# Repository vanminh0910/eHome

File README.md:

# eHome
This is reserved repository for my smart home project

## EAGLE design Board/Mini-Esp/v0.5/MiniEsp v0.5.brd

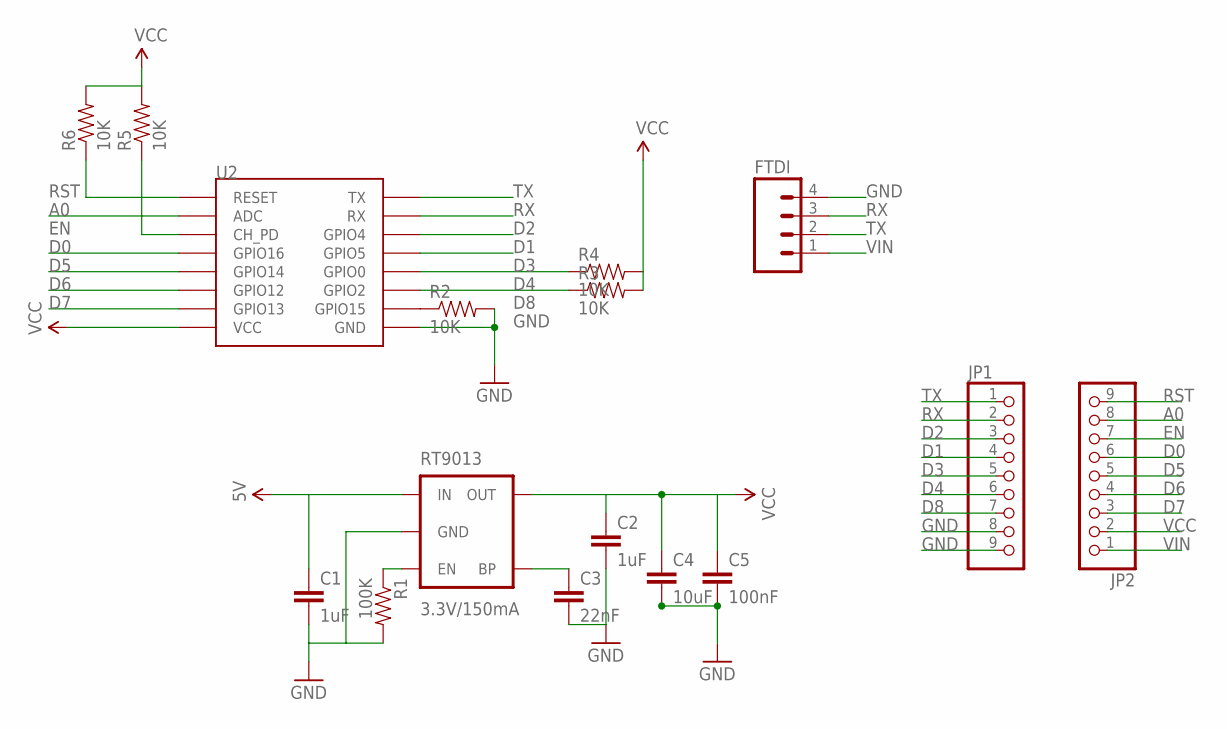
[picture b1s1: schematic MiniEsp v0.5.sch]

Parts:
C1, C2: 1uF; 0805
C3: 22nF; 0805
C4: 10uF; 0805
C5: 100nF; 0805
FTDI: M04PTH; 1X04
JP1, JP2: PINHD-1X9; 1X09-BIG
R1: 100K; 0805
R2, R3, R4, R5, R6: 10K; 0805
RT9013: 3.3V/150mA; SOT23-5
U2: ESP12

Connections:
A0: JP2.8, U2.ADC
BP: C3.1, RT9013.4 (BP)
D0: JP2.6, U2.GPIO16
D1: JP1.4, U2.GPIO5
D2: JP1.3, U2.GPIO4
D3: JP1.5, R4.1, U2.GPIO0
D4: JP1.6, R3.1, U2.GPIO2
D5: JP2.5, U2.GPIO14
D6: JP2.4, U2.GPIO12
D7: JP2.3, U2.GPIO13
D8: JP1.7, R2.1, U2.GPIO15
EN: JP2.7, R5.1, U2.CH_PD
GND: C1.2, C2.2, C3.2, C4.2, C5.2, FTDI.4, JP1.8, JP1.9, R1.2, R2.2, RT9013.2 (GND), U2.GND
LDO_EN: R1.1, RT9013.3 (EN)
RST: JP2.9, R6.1, U2.RESET
RX: FTDI.3, JP1.2, U2.RX
TX: FTDI.2, JP1.1, U2.TX
VCC: C2.1, C4.1, C5.1, JP2.2, R3.2, R4.2, R5.2, R6.2, RT9013.5 (OUT), U2.VCC
VIN: C1.1, FTDI.1, JP2.1, RT9013.1 (IN)

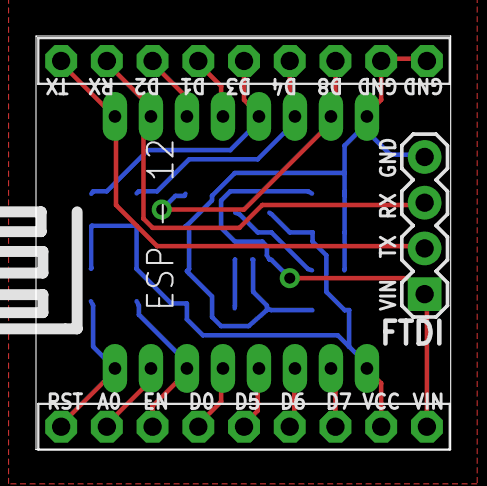
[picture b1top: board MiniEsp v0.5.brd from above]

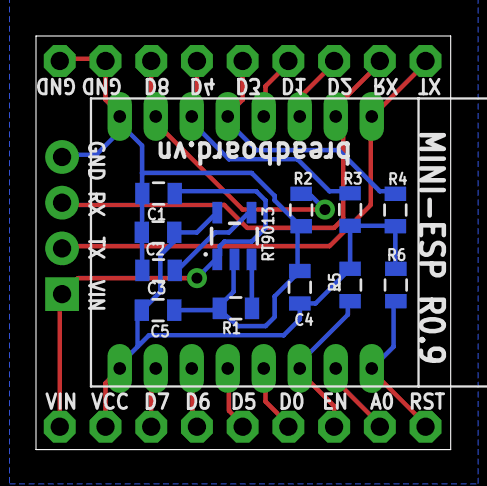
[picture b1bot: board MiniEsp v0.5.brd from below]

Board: 2 copper layers, 23.0 x 23.0 mm, 16 parts (12 on the bottom side), 19 nets.

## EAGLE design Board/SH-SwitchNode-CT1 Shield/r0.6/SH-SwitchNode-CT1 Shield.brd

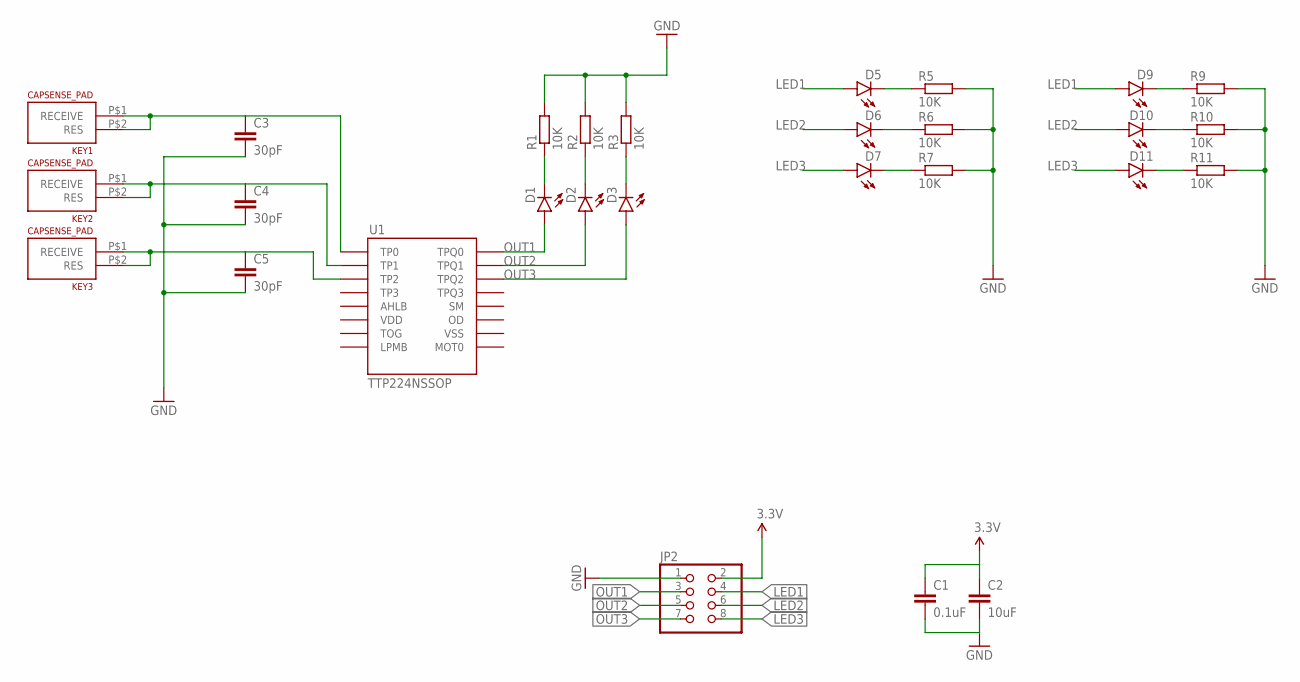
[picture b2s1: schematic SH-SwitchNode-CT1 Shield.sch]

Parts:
C1: 0.1uF; 0805
C2: 10uF; 0805
C3, C4, C5: 30pF; 0805
D1, D2, D3, D5, D6, D7, D9, D10, D11: LED1206-BOTTOM; LED-1206-BOTTOM
JP2: PINHD-2X4; 2X04
KEY1, KEY2, KEY3: CAPSENSE_PAD
R1, R2, R3, R5, R6, R7, R9, R10, R11: 10K; R0805
U1: TTP224NSSOP; SSOP16

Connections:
3.3V: C1.1, C2.1, JP2.2
GND: C1.2, C2.2, C3.2, C4.2, C5.2, JP2.1, R1.2, R2.2, R3.2, R5.2, R6.2, R7.2, R9.2, R10.2, R11.2
KEY1: C3.1, KEY1.P$1 (RECEIVE), KEY1.P$2 (RES), U1.1 (TP0)
KEY2: C4.1, KEY2.P$1 (RECEIVE), KEY2.P$2 (RES), U1.2 (TP1)
KEY3: C5.1, KEY3.P$1 (RECEIVE), KEY3.P$2 (RES), U1.3 (TP2)
LED1: D5.A, D9.A, JP2.4
LED2: D6.A, D10.A, JP2.6
LED3: D7.A, D11.A, JP2.8
unnamed: D5.C, R5.1
unnamed: D6.C, R6.1
unnamed: D1.C, R1.1
unnamed: D7.C, R7.1
unnamed: D9.C, R9.1
unnamed: D2.C, R2.1
unnamed: D3.C, R3.1
unnamed: D10.C, R10.1
unnamed: D11.C, R11.1
OUT1: D1.A, JP2.3, U1.16 (TPQ0)
OUT2: D2.A, JP2.5, U1.15 (TPQ1)
OUT3: D3.A, JP2.7, U1.14 (TPQ2)
VDD: U1.6 (VDD)
VSS: U1.10 (VSS)

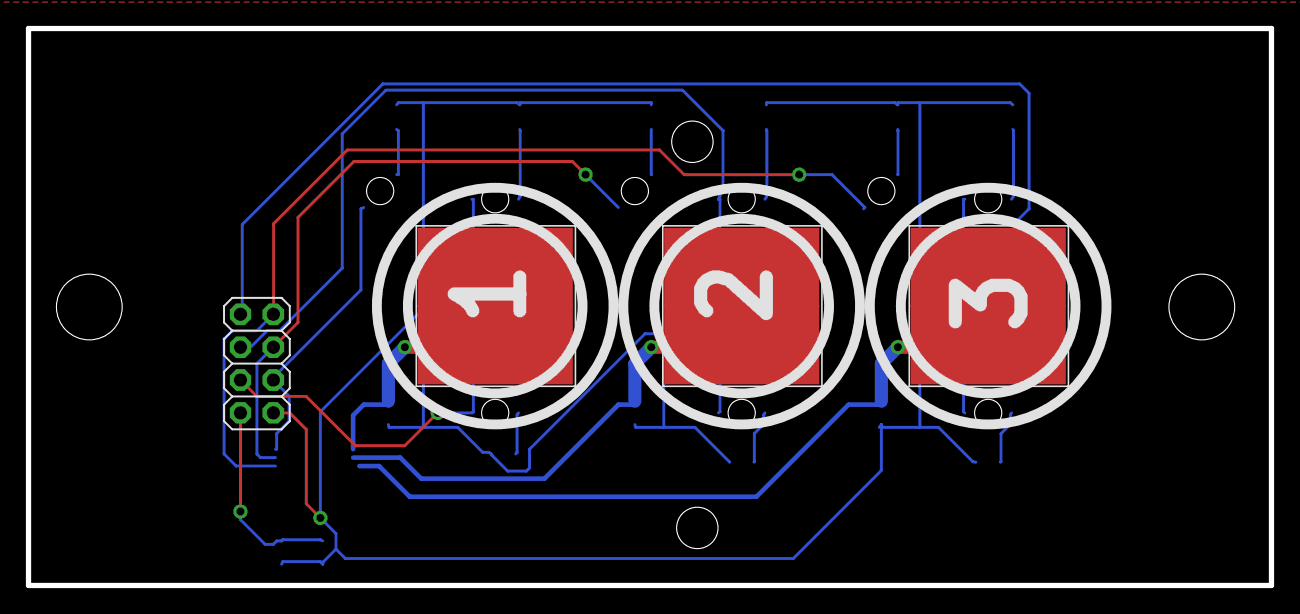
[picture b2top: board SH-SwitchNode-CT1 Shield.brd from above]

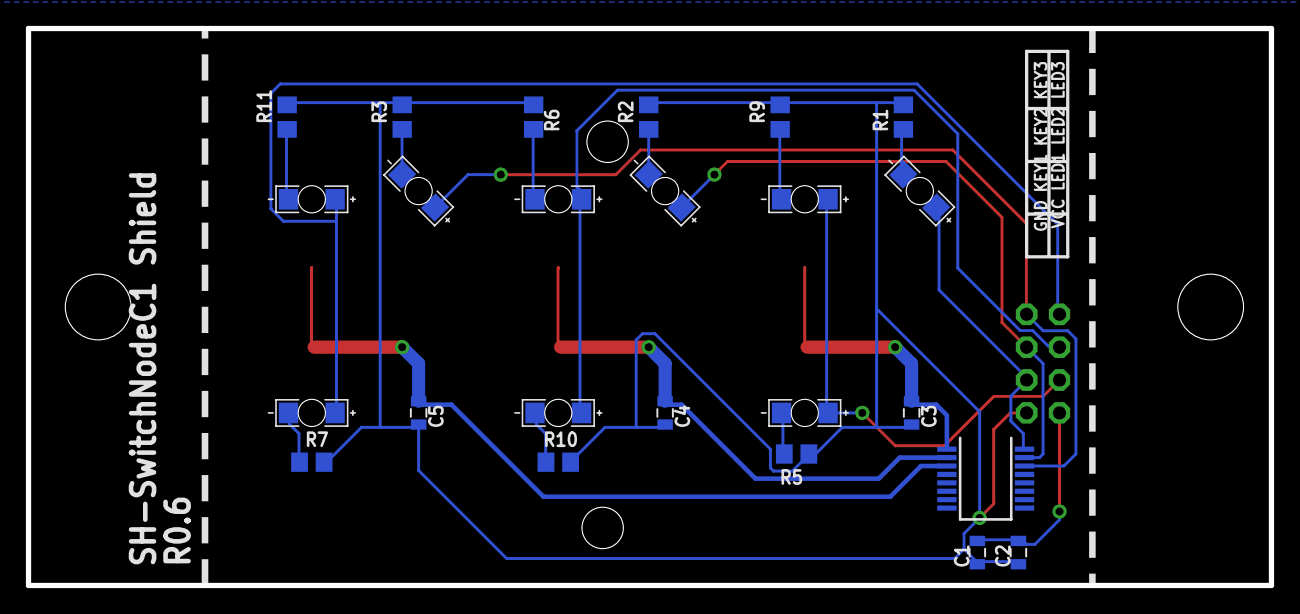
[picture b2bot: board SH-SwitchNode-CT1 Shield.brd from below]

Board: 2 copper layers, 96.1 x 43.0 mm, 28 parts (24 on the bottom side), 20 nets.

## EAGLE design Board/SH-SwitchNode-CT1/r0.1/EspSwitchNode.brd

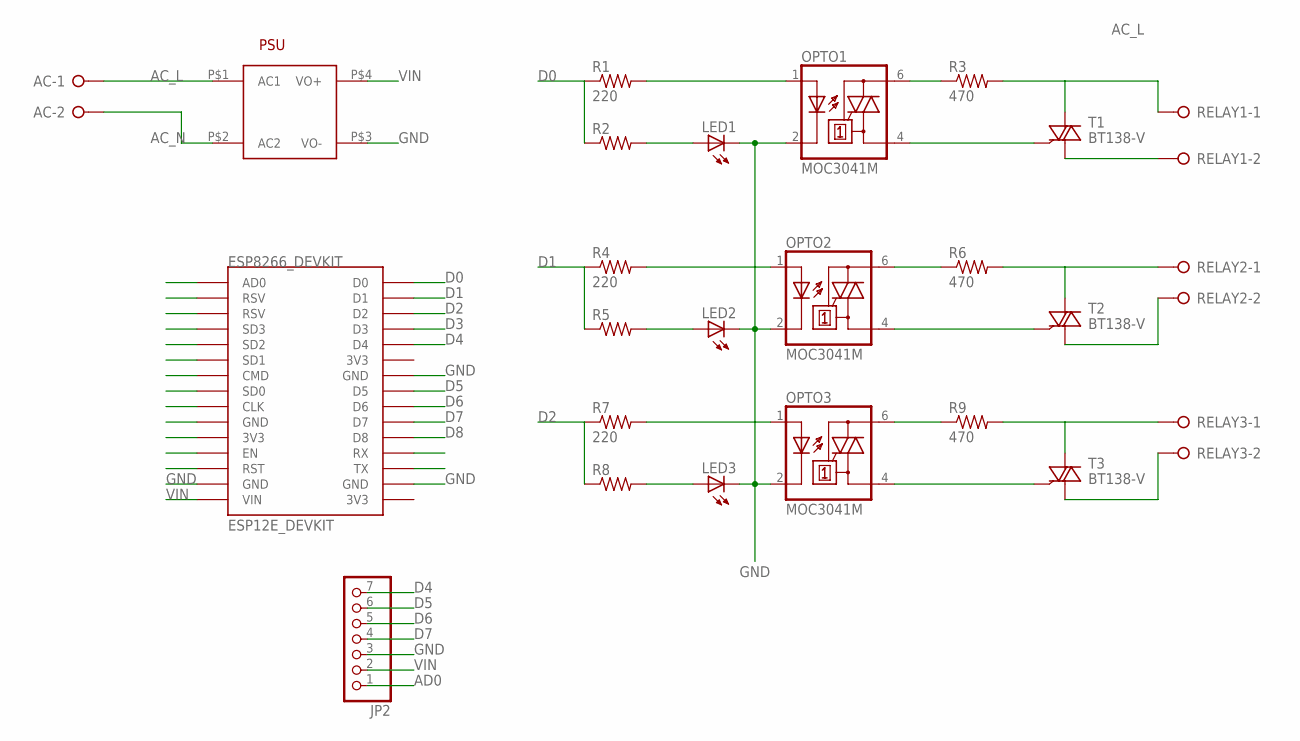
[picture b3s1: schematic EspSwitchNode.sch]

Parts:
AC: W237-02P; W237-132
ESP8266_DEVKIT: ESP12E_DEVKIT
JP2: PINHD-1X7; 1X07
LED1, LED2, LED3: LEDCHIPLED_0805; CHIPLED_0805
OPTO1, OPTO2, OPTO3: MOC3041M; DIL06
PSU: HLK-PM01
R1, R4, R7: 220; M0805
R2, R5, R8: R-US_M0805; M0805
R3, R6, R9: 470; M0805
RELAY1, RELAY2, RELAY3: W237-02P; W237-132
T1, T2, T3: BT138-V; TO220BV

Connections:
3V3: ESP8266_DEVKIT.3V3@0 (3V3)
AC_L: AC.1, PSU.P$1 (AC1), R3.2, R6.2, R9.2, RELAY1.1, RELAY2.1, RELAY3.1, T1.T2 (A2), T2.T2 (A2), T3.T2 (A2)
AC_N: AC.2, PSU.P$2 (AC2)
AD0: ESP8266_DEVKIT.AD0, JP2.1
CLK: ESP8266_DEVKIT.CLK
CMD: ESP8266_DEVKIT.CMD
D0: ESP8266_DEVKIT.D0, R1.1, R2.1
D1: ESP8266_DEVKIT.D1, R4.1, R5.1
D2: ESP8266_DEVKIT.D2, R7.1, R8.1
D3: ESP8266_DEVKIT.D3
D4: ESP8266_DEVKIT.D4, JP2.7
D5: ESP8266_DEVKIT.D5, JP2.6
D6: ESP8266_DEVKIT.D6, JP2.5
D7: ESP8266_DEVKIT.D7, JP2.4
D8: ESP8266_DEVKIT.D8
EN: ESP8266_DEVKIT.EN
GND: ESP8266_DEVKIT.GND@0 (GND), ESP8266_DEVKIT.GND@1 (GND), ESP8266_DEVKIT.GND@2 (GND), ESP8266_DEVKIT.GND@3 (GND), JP2.3, LED1.C, LED2.C, LED3.C, OPTO1.2 (C), OPTO2.2 (C), OPTO3.2 (C), PSU.P$3 (VO-)
unnamed: OPTO1.1 (A), R1.2
unnamed: OPTO1.6 (A2), R3.1
unnamed: OPTO2.1 (A), R4.2
unnamed: LED2.A, R5.2
unnamed: OPTO2.6 (A2), R6.1
unnamed: OPTO1.4 (A1), T1.G
unnamed: OPTO2.4 (A1), T2.G
unnamed: OPTO3.1 (A), R7.2
unnamed: LED3.A, R8.2
unnamed: RELAY2.2, T2.T1 (A1)
unnamed: OPTO3.6 (A2), R9.1
unnamed: OPTO3.4 (A1), T3.G
unnamed: RELAY3.2, T3.T1 (A1)
unnamed: LED1.A, R2.2
unnamed: RELAY1.2, T1.T1 (A1)
RST: ESP8266_DEVKIT.RST
RX: ESP8266_DEVKIT.RX
SD0: ESP8266_DEVKIT.SD0
SD1: ESP8266_DEVKIT.SD1
SD2: ESP8266_DEVKIT.SD2
SD3: ESP8266_DEVKIT.SD3
TX: ESP8266_DEVKIT.TX
VIN: ESP8266_DEVKIT.VIN, JP2.2, PSU.P$4 (VO+)

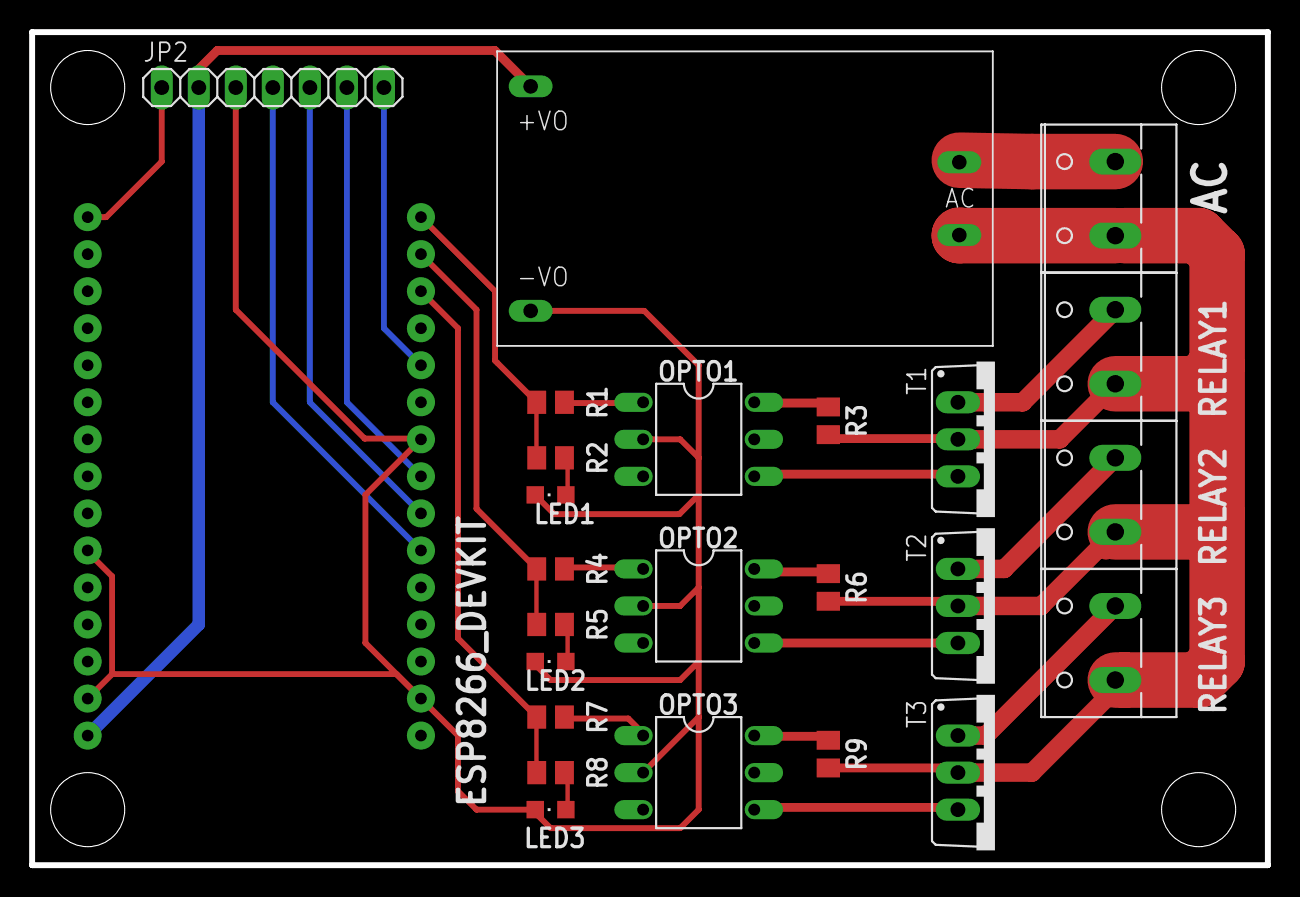
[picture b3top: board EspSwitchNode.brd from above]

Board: 2 copper layers, 84.8 x 57.1 mm, 25 parts (0 on the bottom side), 27 nets.

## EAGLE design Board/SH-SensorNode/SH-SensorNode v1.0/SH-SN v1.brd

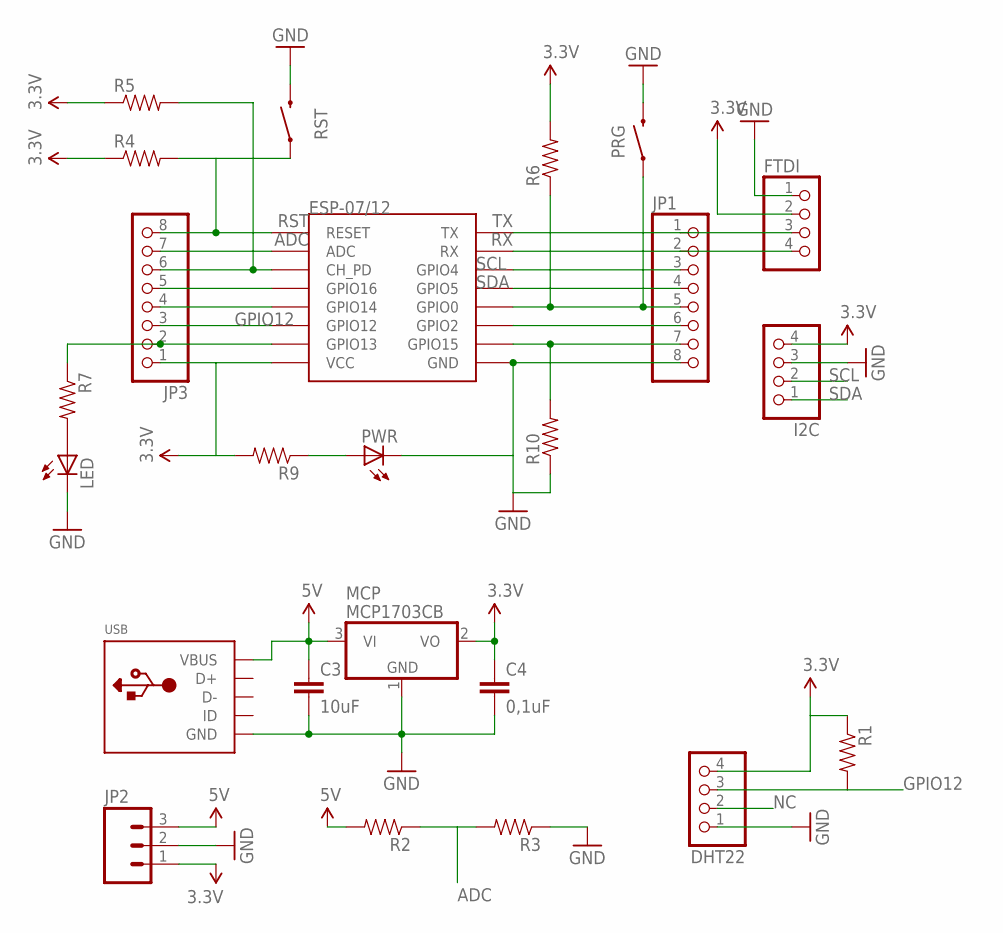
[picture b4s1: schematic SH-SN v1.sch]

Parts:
C3: 10uF; 0805
C4: 0,1uF; 0805
DHT22: PINHD-1X4; 1X04
ESP-07/12: ESP12SMD; ESP12-SMD
FTDI: PINHD-1X4; 1X04
I2C: PINHD-1X4; 1X04
JP1, JP3: PINHD-1X8; 1X08
JP2: M03SCREW; SCREWTERMINAL-3.5MM-3
LED: LEDCHIPLED_0805; CHIPLED_0805
MCP: MCP1703CB; SOT23
PRG: SWITCH-MOMENTARY-2SMD-REDUNDANT; TACTILE-SWITCH-SMD
PWR: LEDCHIPLED_0805; CHIPLED_0805
R1, R2, R3, R4, R5, R6, R7, R9, R10: RESISTOR0805-RES; 0805
RST: SWITCH-MOMENTARY-2SMD-REDUNDANT; TACTILE-SWITCH-SMD
USB: USBMINIB; USB-MINIB

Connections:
3.3V: C4.1, ESP-07/12.VCC, FTDI.2, I2C.4, JP2.1, JP3.1, MCP.2 (VO), R4.1, R5.1, R6.2, R9.2
5V: C3.1, JP2.3, MCP.3 (VI), R2.2, USB.VBUS
ADC: ESP-07/12.ADC, JP3.7, R2.1, R3.2
GND: C3.2, C4.2, DHT22.1, ESP-07/12.GND, FTDI.1, I2C.3, JP1.8, JP2.2, LED.C, MCP.1 (GND), PRG.3 (2), PRG.4 (2), PWR.C, R3.1, R10.1, RST.3 (2), RST.4 (2), USB.GND
GPIO0: ESP-07/12.GPIO13, JP3.2, R7.1
GPIO12: DHT22.3, DHT22.4, ESP-07/12.GPIO12, JP3.3, R1.1, R1.2
unnamed: ESP-07/12.GPIO14, JP3.4
unnamed: ESP-07/12.GPIO2, JP1.6
unnamed: ESP-07/12.GPIO0, JP1.5, PRG.1, PRG.2 (1), R6.1
unnamed: ESP-07/12.CH_PD, JP3.6, R5.2
unnamed: ESP-07/12.GPIO16, JP3.5
unnamed: ESP-07/12.GPIO15, JP1.7, R10.2
unnamed: LED.A, R7.2
unnamed: PWR.A, R9.1
NC: DHT22.2
RST: ESP-07/12.RESET, JP3.8, R4.2, RST.1, RST.2 (1)
RX: ESP-07/12.RXD0 (RX), FTDI.4, JP1.2
SCL: ESP-07/12.GPIO4, I2C.2, JP1.3
SDA: ESP-07/12.GPIO5, I2C.1, JP1.4
TX: ESP-07/12.TXD0 (TX), FTDI.3, JP1.1

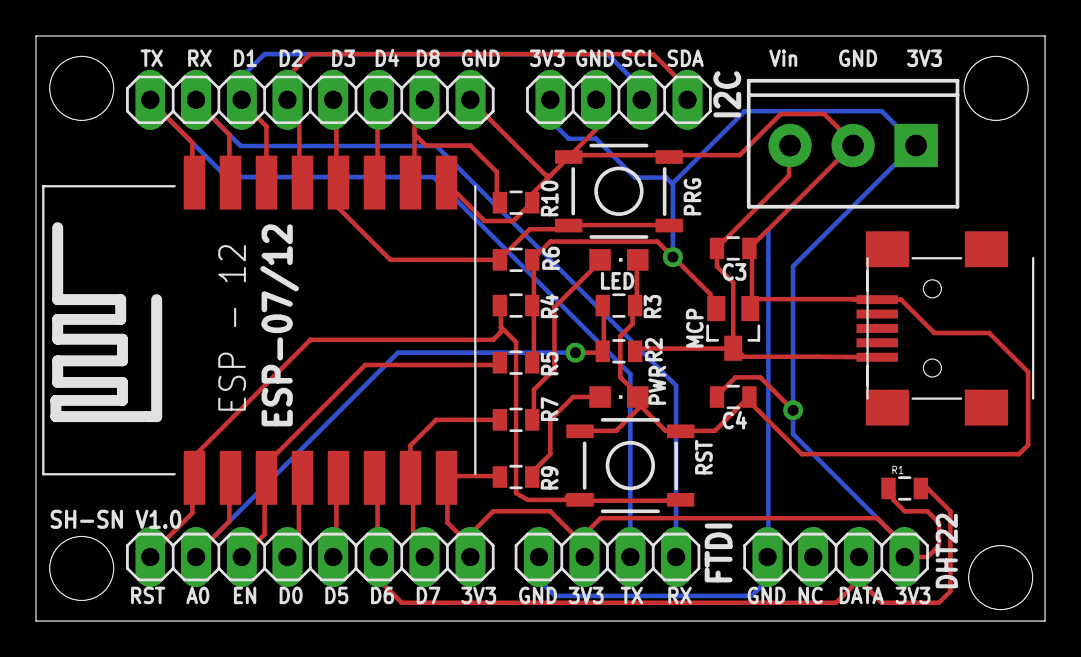
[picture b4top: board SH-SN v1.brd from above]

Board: 2 copper layers, 56.1 x 32.5 mm, 24 parts (0 on the bottom side), 19 nets.

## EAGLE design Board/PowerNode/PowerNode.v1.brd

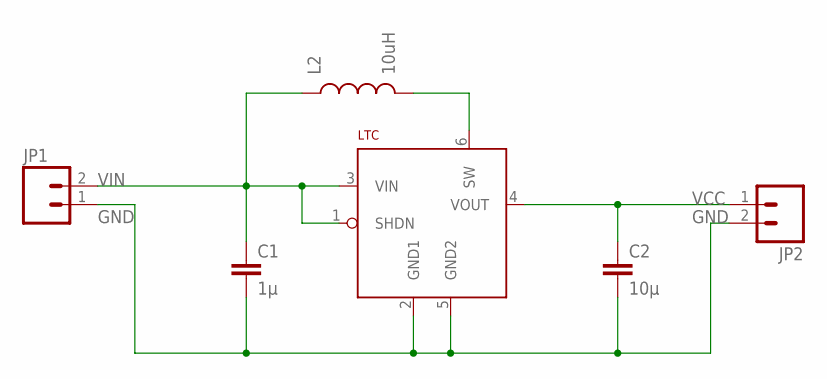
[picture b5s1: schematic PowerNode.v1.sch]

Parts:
C1: 1µ; 0603-CAP
C2: 10µ; 0805
JP1, JP2: M02PTH; 1X02
L2: 10uH; CR54
LTC: LTC3525; SC70

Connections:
GND: C1.2, C2.2, JP1.1, JP2.2, LTC.2 (GND1), LTC.5 (GND2)
unnamed: L2.P$2 (2), LTC.6 (SW)
VCC: C2.1, JP2.1, LTC.4 (VOUT)
VIN: C1.1, JP1.2, L2.P$1 (1), LTC.1 (SHDN), LTC.3 (VIN)

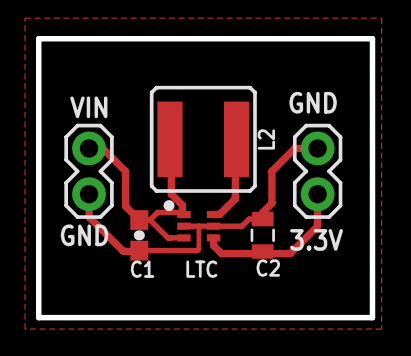
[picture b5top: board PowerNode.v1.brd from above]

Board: 2 copper layers, 18.5 x 15.5 mm, 6 parts (0 on the bottom side), 4 nets.

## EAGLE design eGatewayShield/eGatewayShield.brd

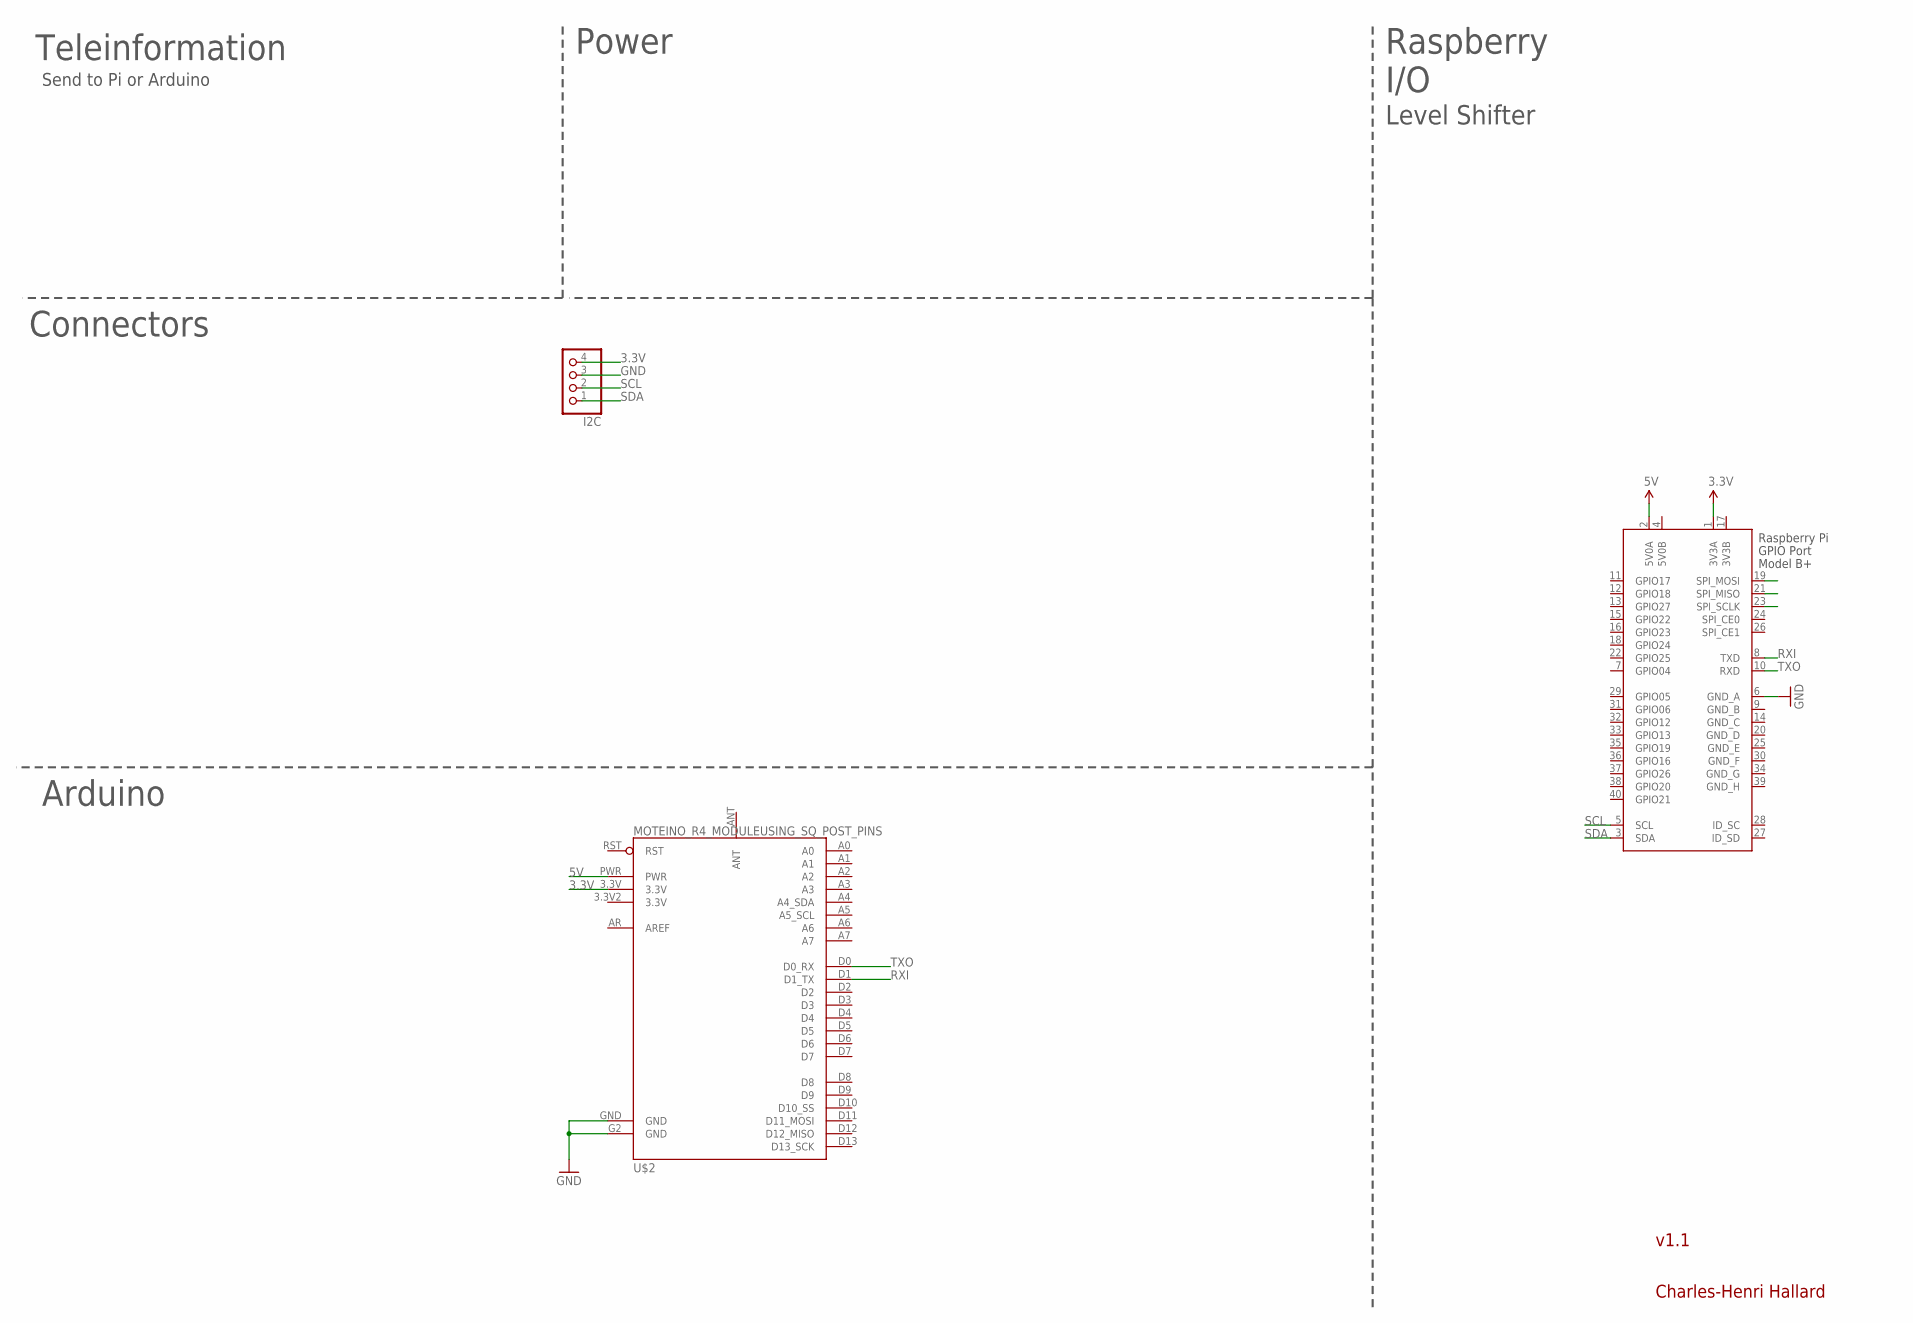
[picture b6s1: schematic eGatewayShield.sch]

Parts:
I2C: PINHD-1X4; 1X04
U$2: MOTEINO_R4_MODULEUSING_SQ_POST_PINS; MOTEINTO_R4_SQ
X1: RASPI_BOARD_B+#_F; RASPI_BOARD_B+_FULL

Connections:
3.3V: I2C.4, U$2.3.3V, X1.1 (3V3A)
3V3B: X1.17 (3V3B)
5V: U$2.PWR, X1.2 (5V0A)
5V0B: X1.4 (5V0B)
GND: I2C.3, U$2.G2 (GND), U$2.GND, X1.6 (GND_A)
GND_B: X1.9 (GND_B)
GND_C: X1.14 (GND_C)
GND_D: X1.20 (GND_D)
GND_E: X1.25 (GND_E)
GND_F: X1.30 (GND_F)
GND_G: X1.34 (GND_G)
GND_H: X1.39 (GND_H)
RXI: U$2.D1 (D1_TX), X1.8 (TXD)
SCL: I2C.2, X1.5 (SCL)
SDA: I2C.1, X1.3 (SDA)
TXO: U$2.D0 (D0_RX), X1.10 (RXD)

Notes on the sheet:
Teleinformation
Power
Charles-Henri Hallard
Raspberry I/O
Level Shifter
Send to Pi or Arduino
Connectors
Arduino
v1.1

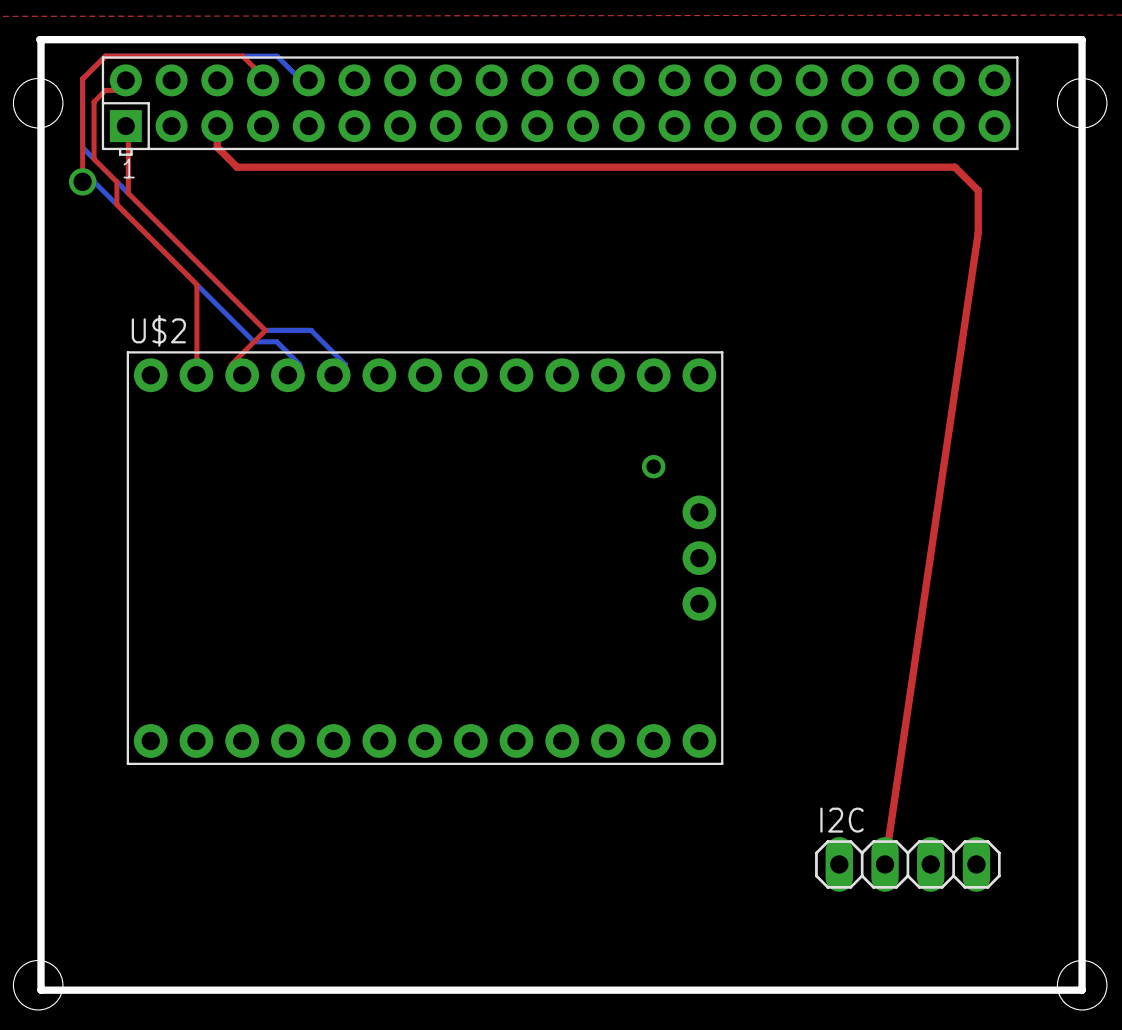
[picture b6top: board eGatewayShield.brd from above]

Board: 2 copper layers, 57.9 x 52.8 mm, 3 parts (0 on the bottom side), 7 nets.

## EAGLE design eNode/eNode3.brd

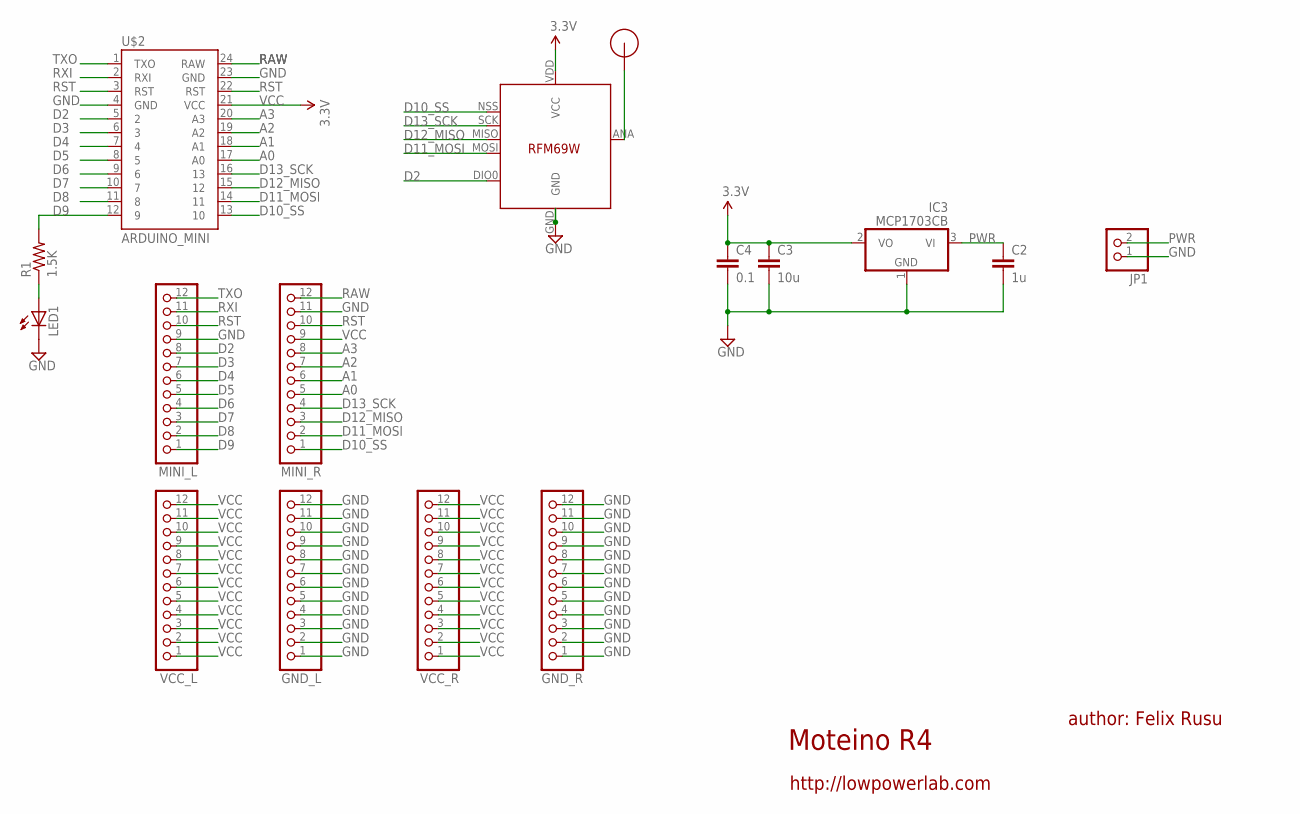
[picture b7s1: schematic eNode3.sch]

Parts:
C2: 1u; 0603-CAP
C3: 10u; 0805-CAP
C4: 0.1; 0603-CAP
GND_L: PINHD-1X12-CB; 1X12-CB
GND_R: PINHD-1X12-CB; 1X12-CB
IC3: MCP1703CB; SOT23
JP1: PINHD-1X2; 1X02
LED1: LED3MM
MINI_L: PINHD-1X12-CB; 1X12-CB
MINI_R: PINHD-1X12-CB; 1X12-CB
R1: 1.5K; R0805
U$1: RFM12B_ANTENNA; RFM12B-ANTENNA
U$2: ARDUINO_MINI
U$5: RFM69; RFM69W-MINPADS
VCC_L: PINHD-1X12-CB; 1X12-CB
VCC_R: PINHD-1X12-CB; 1X12-CB

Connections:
A0: MINI_R.5, U$2.17 (A0)
A1: MINI_R.6, U$2.18 (A1)
A2: MINI_R.7, U$2.19 (A2)
A3: MINI_R.8, U$2.20 (A3)
D2: MINI_L.8, U$2.5 (2), U$5.DIO0
D3: MINI_L.7, U$2.6 (3)
D4: MINI_L.6, U$2.7 (4)
D5: MINI_L.5, U$2.8 (5)
D6: MINI_L.4, U$2.9 (6)
D7: MINI_L.3, U$2.10 (7)
D8: MINI_L.2, U$2.11 (8)
D9: MINI_L.1, R1.2, U$2.12 (9)
D10_SS: MINI_R.1, U$2.13 (10), U$5.NSS (SEL)
D11_MOSI: MINI_R.2, U$2.14 (11), U$5.MOSI
D12_MISO: MINI_R.3, U$2.15 (12), U$5.MISO
D13_SCK: MINI_R.4, U$2.16 (13), U$5.SCK
GND: C2.2, C3.2, C4.2, GND_L.1, GND_L.2, GND_L.3, GND_L.4, GND_L.5, GND_L.6, GND_L.7, GND_L.8, GND_L.9, GND_L.10, GND_L.11, GND_L.12, GND_R.1, GND_R.2, GND_R.3, GND_R.4, GND_R.5, GND_R.6, GND_R.7, GND_R.8, GND_R.9, GND_R.10, GND_R.11, GND_R.12, IC3.1 (GND), JP1.1, LED1.K (C), MINI_L.9, MINI_R.11, U$2.4 (GND), U$2.23 (GND), U$5.GND
unnamed: LED1.A, R1.1
unnamed: U$1.P$1, U$5.ANA (ANT)
PWR: C2.1, IC3.3 (VI), JP1.2
RAW: MINI_R.12, U$2.24 (RAW)
RST: MINI_L.10, MINI_R.10, U$2.3 (RST), U$2.22 (RST)
RXI: MINI_L.11, U$2.2 (RXI)
TXO: MINI_L.12, U$2.1 (TXO)
VCC: C3.1, C4.1, IC3.2 (VO), MINI_R.9, U$2.21 (VCC), U$5.VDD (VCC), VCC_L.1, VCC_L.2, VCC_L.3, VCC_L.4, VCC_L.5, VCC_L.6, VCC_L.7, VCC_L.8, VCC_L.9, VCC_L.10, VCC_L.11, VCC_L.12, VCC_R.1, VCC_R.2, VCC_R.3, VCC_R.4, VCC_R.5, VCC_R.6, VCC_R.7, VCC_R.8, VCC_R.9, VCC_R.10, VCC_R.11, VCC_R.12

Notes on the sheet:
Moteino R4
author: Felix Rusu
http://lowpowerlab.com

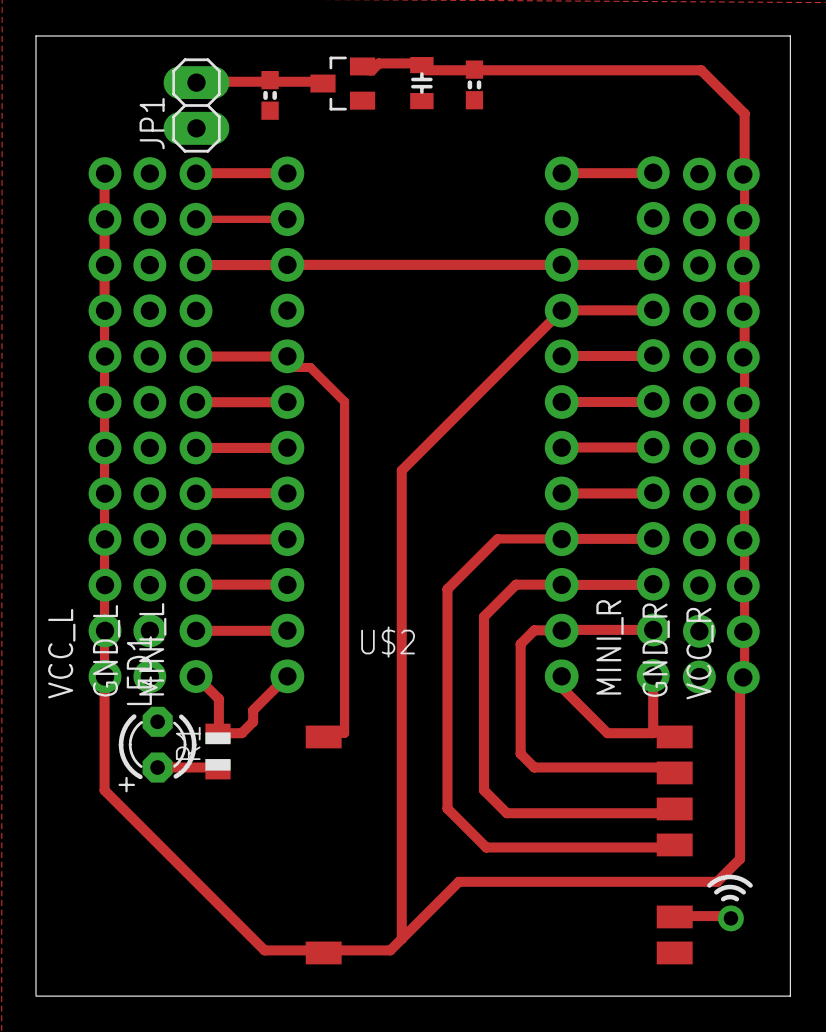
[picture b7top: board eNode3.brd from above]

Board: 2 copper layers, 41.9 x 53.3 mm, 16 parts (0 on the bottom side), 25 nets.

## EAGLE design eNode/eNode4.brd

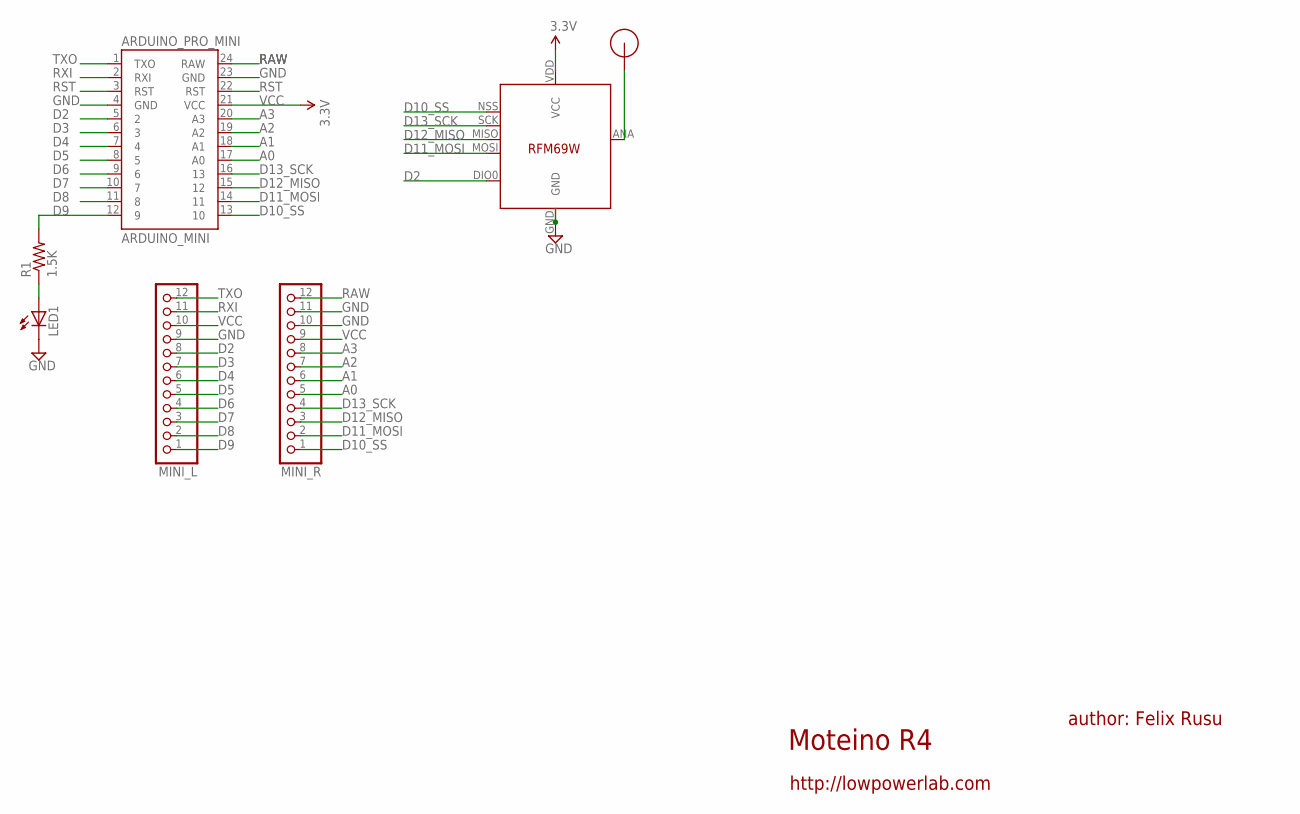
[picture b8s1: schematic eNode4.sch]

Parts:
ARDUINO_PRO_MINI: ARDUINO_MINI
LED1: LED3MM
MINI_L: PINHD-1X12-CB; 1X12-CB
MINI_R: PINHD-1X12-CB; 1X12-CB
R1: 1.5K; R0805
U$1: RFM12B_ANTENNA; RFM12B-ANTENNA
U$5: RFM69; RFM69W-MINPADS

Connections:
A0: ARDUINO_PRO_MINI.17 (A0), MINI_R.5
A1: ARDUINO_PRO_MINI.18 (A1), MINI_R.6
A2: ARDUINO_PRO_MINI.19 (A2), MINI_R.7
A3: ARDUINO_PRO_MINI.20 (A3), MINI_R.8
D2: ARDUINO_PRO_MINI.5 (2), MINI_L.8, U$5.DIO0
D3: ARDUINO_PRO_MINI.6 (3), MINI_L.7
D4: ARDUINO_PRO_MINI.7 (4), MINI_L.6
D5: ARDUINO_PRO_MINI.8 (5), MINI_L.5
D6: ARDUINO_PRO_MINI.9 (6), MINI_L.4
D7: ARDUINO_PRO_MINI.10 (7), MINI_L.3
D8: ARDUINO_PRO_MINI.11 (8), MINI_L.2
D9: ARDUINO_PRO_MINI.12 (9), MINI_L.1, R1.2
D10_SS: ARDUINO_PRO_MINI.13 (10), MINI_R.1, U$5.NSS (SEL)
D11_MOSI: ARDUINO_PRO_MINI.14 (11), MINI_R.2, U$5.MOSI
D12_MISO: ARDUINO_PRO_MINI.15 (12), MINI_R.3, U$5.MISO
D13_SCK: ARDUINO_PRO_MINI.16 (13), MINI_R.4, U$5.SCK
GND: ARDUINO_PRO_MINI.4 (GND), ARDUINO_PRO_MINI.23 (GND), LED1.K (C), MINI_L.9, MINI_R.10, MINI_R.11, U$5.GND
unnamed: LED1.A, R1.1
unnamed: U$1.P$1, U$5.ANA (ANT)
RAW: ARDUINO_PRO_MINI.24 (RAW), MINI_R.12
RST: ARDUINO_PRO_MINI.3 (RST), ARDUINO_PRO_MINI.22 (RST)
RXI: ARDUINO_PRO_MINI.2 (RXI), MINI_L.11
TXO: ARDUINO_PRO_MINI.1 (TXO), MINI_L.12
VCC: ARDUINO_PRO_MINI.21 (VCC), MINI_L.10, MINI_R.9, U$5.VDD (VCC)

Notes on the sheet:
Moteino R4
author: Felix Rusu
http://lowpowerlab.com

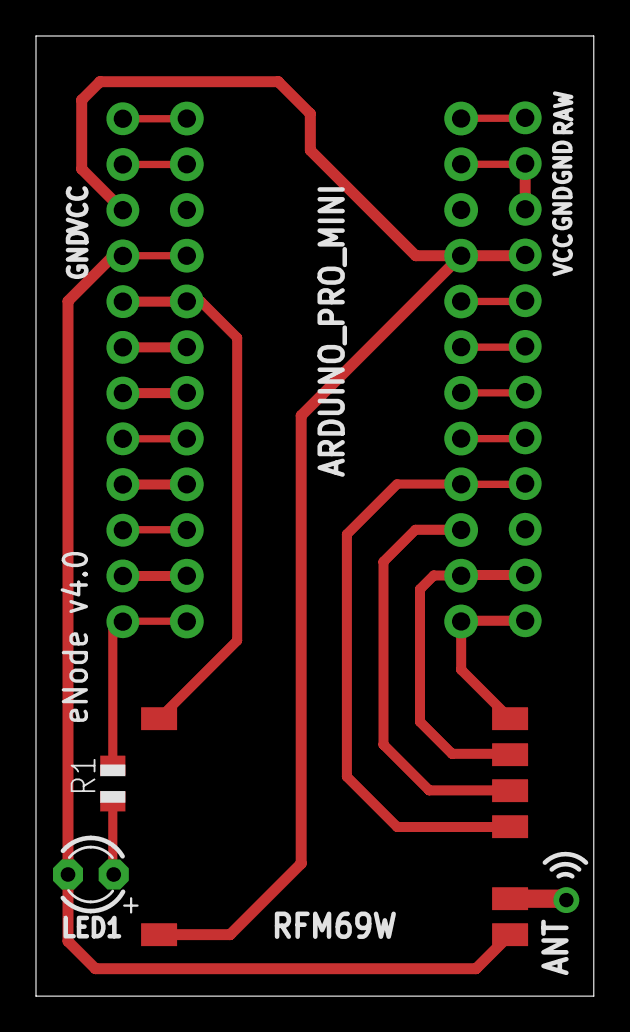
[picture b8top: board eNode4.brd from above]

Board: 2 copper layers, 31.0 x 53.3 mm, 7 parts (0 on the bottom side), 24 nets.

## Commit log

2015-04-02 :confetti_ball: Added .gitattributes
2015-04-02 Create newfile
2015-04-02 Create new folder structure
2015-04-02 Create gh-pages branch via GitHub
2015-04-14 Add schematic and board of eNode v1
2015-04-17 Update eNode board and schematic
2015-04-29 Update final eNode version 1
2015-05-13 Add bunch of misc file and server init version
2015-05-13 Commit remaining files from last commit
2015-07-31 Add Backup files from old smart home project
2016-02-15 Added some new boards
2016-02-22 Add Wemos D1 Mini.lbr
2016-02-23 Add outside button circle label
2016-04-04 Add Mini-Esp version 1.0
2016-04-04 Rename MiniEsp to Mini-Esp
2016-08-16 Update wemo simulator
2016-09-26 Remove unused files
2017-08-28 Update echo mqtt

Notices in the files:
parts and their libraries:
SparkFun-Passives: Licensing: Creative Commons ShareAlike 4.0 International - https://creativecommons.org/licenses/by-sa/4.0
SparkFun: Licensing: CC v3.0 Share-Alike You are welcome to use this library for commercial purposes.
